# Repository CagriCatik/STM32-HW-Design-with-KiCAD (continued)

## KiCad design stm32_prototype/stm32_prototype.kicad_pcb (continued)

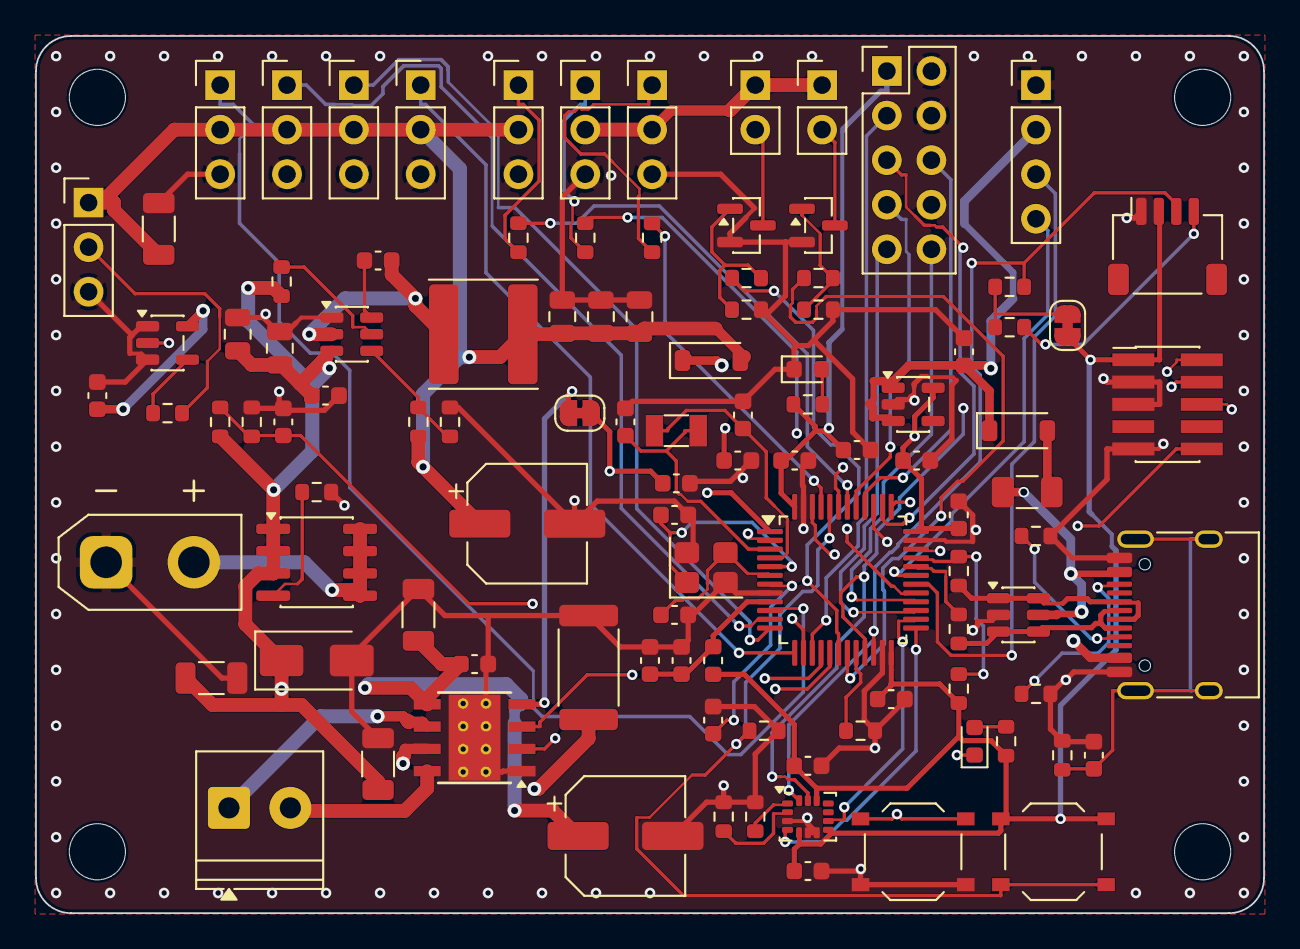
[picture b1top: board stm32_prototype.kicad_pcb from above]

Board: 4 copper layers, 70.0 x 50.0 mm, 108 parts (0 on the bottom side), 76 nets.

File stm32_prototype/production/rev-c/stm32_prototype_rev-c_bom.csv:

"Comment","Designator","Footprint","LCSC Part #"
"100n","C1,C2,C3,C5,C12,C15,C18,C19,C29,C31,C32,C33","Capacitor_SMD:C_0603_1608Metric","C14663"
"4.7u","C4","Capacitor_SMD:C_0603_1608Metric","C19666"
"10n","C6","Capacitor_SMD:C_0603_1608Metric","C57112"
"1u","C7,C24,C25","Capacitor_SMD:C_0603_1608Metric","C15849"
"15p","C8,C9","Capacitor_SMD:C_0603_1608Metric","C1644"
"22u 25V","C13,C14,C28,C34","Capacitor_SMD:C_1206_3216Metric","C12891"
"10u 25V","C16,C17","Capacitor_SMD:C_0805_2012Metric","C15850"
"22u 25V","C20,C21,C22","Capacitor_SMD:C_0805_2012Metric","C45783"
"4.7n","C23","Capacitor_SMD:C_0603_1608Metric","C53987"
"10u","C26","Capacitor_SMD:C_0603_1608Metric","C19702"
"100u 25V","C27,C30","Capacitor_SMD:CP_Elec_6.3x7.7","C72477"
"red","D1,D5","LED_SMD:LED_0603_1608Metric","C2286"
"SMAJ15A","D2","Diode_SMD:D_SMA","C353478"
"B5819W","D3,D4","Diode_SMD:D_SOD-123","C8598"
"500mA","F1","Fuse:Fuse_1206_3216Metric","C70077"
"600R@100MHz","FB1","Inductor_SMD:L_0603_1608Metric","C1002"
"XT30 battery 2S-3S","J1","Connector_AMASS:AMASS_XT30UPB-M_1x02_P5.0mm_Vertical","C428721"
"USB-C","J2","Connector_USB:USB_C_Receptacle_HRO_TYPE-C-31-M-12","C165948"
"MOTOR","J3","TerminalBlock_Phoenix:TerminalBlock_Phoenix_PT-1,5-2-3.5-H_1x02_P3.50mm_Horizontal","C474892"
"SERVO1","J4","Connector_PinHeader_2.54mm:PinHeader_1x03_P2.54mm_Vertical","C49257"
"SERVO2","J5","Connector_PinHeader_2.54mm:PinHeader_1x03_P2.54mm_Vertical","C49257"
"SERVO3","J6","Connector_PinHeader_2.54mm:PinHeader_1x03_P2.54mm_Vertical","C49257"
"SERVO4","J7","Connector_PinHeader_2.54mm:PinHeader_1x03_P2.54mm_Vertical","C49257"
"RC1","J8","Connector_PinHeader_2.54mm:PinHeader_1x03_P2.54mm_Vertical","C49257"
"RC2","J9","Connector_PinHeader_2.54mm:PinHeader_1x03_P2.54mm_Vertical","C49257"
"RC3","J10","Connector_PinHeader_2.54mm:PinHeader_1x03_P2.54mm_Vertical","C49257"
"LIGHT1","J11","Connector_PinHeader_2.54mm:PinHeader_1x02_P2.54mm_Vertical","C492401"
"LIGHT2","J12","Connector_PinHeader_2.54mm:PinHeader_1x02_P2.54mm_Vertical","C492401"
"Cortex-Debug","J13","Connector_PinHeader_1.27mm:PinHeader_2x05_P1.27mm_Vertical_SMD","C2935458"
"Qwiic","J14","Connector_JST:JST_SH_SM04B-SRSS-TB_1x04-1MP_P1.00mm_Horizontal","C160404"
"UART","J15","Connector_PinHeader_2.54mm:PinHeader_1x04_P2.54mm_Vertical","C2691448"
"WS2812","J17","Connector_PinHeader_2.54mm:PinHeader_1x03_P2.54mm_Vertical","C49257"
"3.3u","L1","Inductor_SMD:L_Sunlord_SWPA6045S","C83456"
"AO4407A","Q1","Package_SO:SOIC-8_3.9x4.9mm_P1.27mm","C16072"
"AO3400A","Q2,Q3","Package_TO_SOT_SMD:SOT-23","C20917"
"10k","R1,R2,R7,R9,R12,R25,R26","Resistor_SMD:R_0603_1608Metric","C25804"
"1k","R3,R16,R18,R19,R20","Resistor_SMD:R_0603_1608Metric","C21190"
"0R","R4,R5","Resistor_SMD:R_0603_1608Metric","C21189"
"1.5k","R6","Resistor_SMD:R_0603_1608Metric","C22843"
"33k","R8","Resistor_SMD:R_0603_1608Metric","C4216"
"100k","R10,R22,R24","Resistor_SMD:R_0603_1608Metric","C25803"
"56k","R11","Resistor_SMD:R_0603_1608Metric","C23206"
"5.1k","R13,R14","Resistor_SMD:R_0603_1608Metric","C23186"
"1M","R15","Resistor_SMD:R_0603_1608Metric","C22935"
"0.1R 2W","R17","Resistor_SMD:R_2512_6332Metric","C160587"
"100R","R21,R23","Resistor_SMD:R_0603_1608Metric","C22775"
"4.7k","R27,R28","Resistor_SMD:R_0603_1608Metric","C23162"
"330R","R29","Resistor_SMD:R_0603_1608Metric","C23138"
"BOOT0","SW1","Button_Switch_SMD:SW_Push_1P1T_XKB_TS-1187A","C318884"
"RESET","SW2","Button_Switch_SMD:SW_Push_1P1T_XKB_TS-1187A","C318884"
"STM32F103C8T6","U1","Package_QFP:LQFP-48_7x7mm_P0.5mm","C8734"
"TPS563201","U2","Package_TO_SOT_SMD:TSOT-23-6","C116592"
"USBLC6-2SC6","U3","Package_TO_SOT_SMD:SOT-23-6","C7519"
"AP2112K-3.3","U4","Package_TO_SOT_SMD:SOT-23-5","C51118"
"DRV8870","U5","Package_SO:Texas_HSOP-8-1EP_3.9x4.9mm_P1.27mm_ThermalVias","C86590"
"LSM6DS3TR-C","U6","Package_LGA:LGA-14_3x2.5mm_P0.5mm_LayoutBorder3x4y","C967633"
"SN74AHCT1G125","U7","Package_TO_SOT_SMD:SOT-23-5","C7484"
"8MHz","Y1","Crystal:Crystal_SMD_3225-4Pin_3.2x2.5mm","C2682775"

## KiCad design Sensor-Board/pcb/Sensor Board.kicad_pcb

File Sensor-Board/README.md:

# KiCAD_Sensor_Board
Gyroscope, accelerometer, magnetometer and imu sensor expansion board PCB design by usig KiCAD tool.

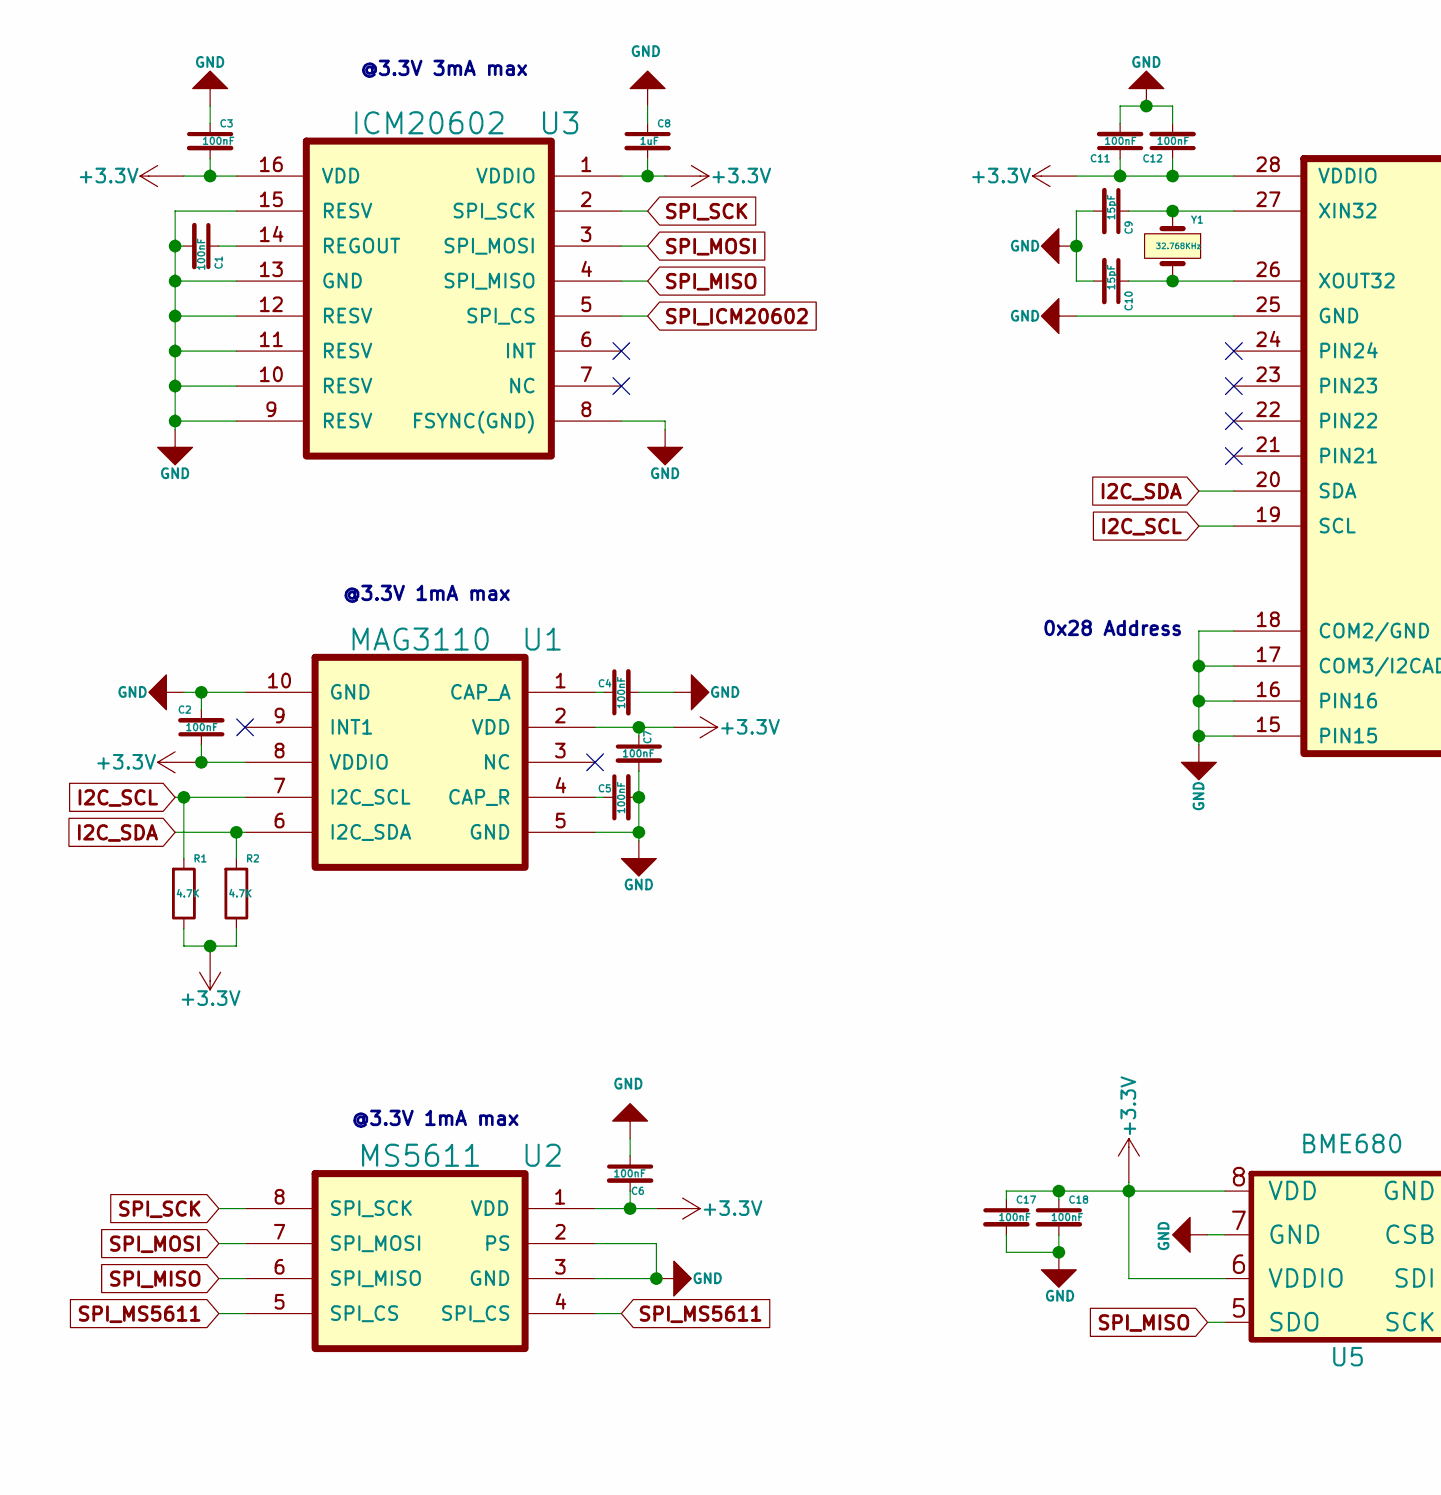
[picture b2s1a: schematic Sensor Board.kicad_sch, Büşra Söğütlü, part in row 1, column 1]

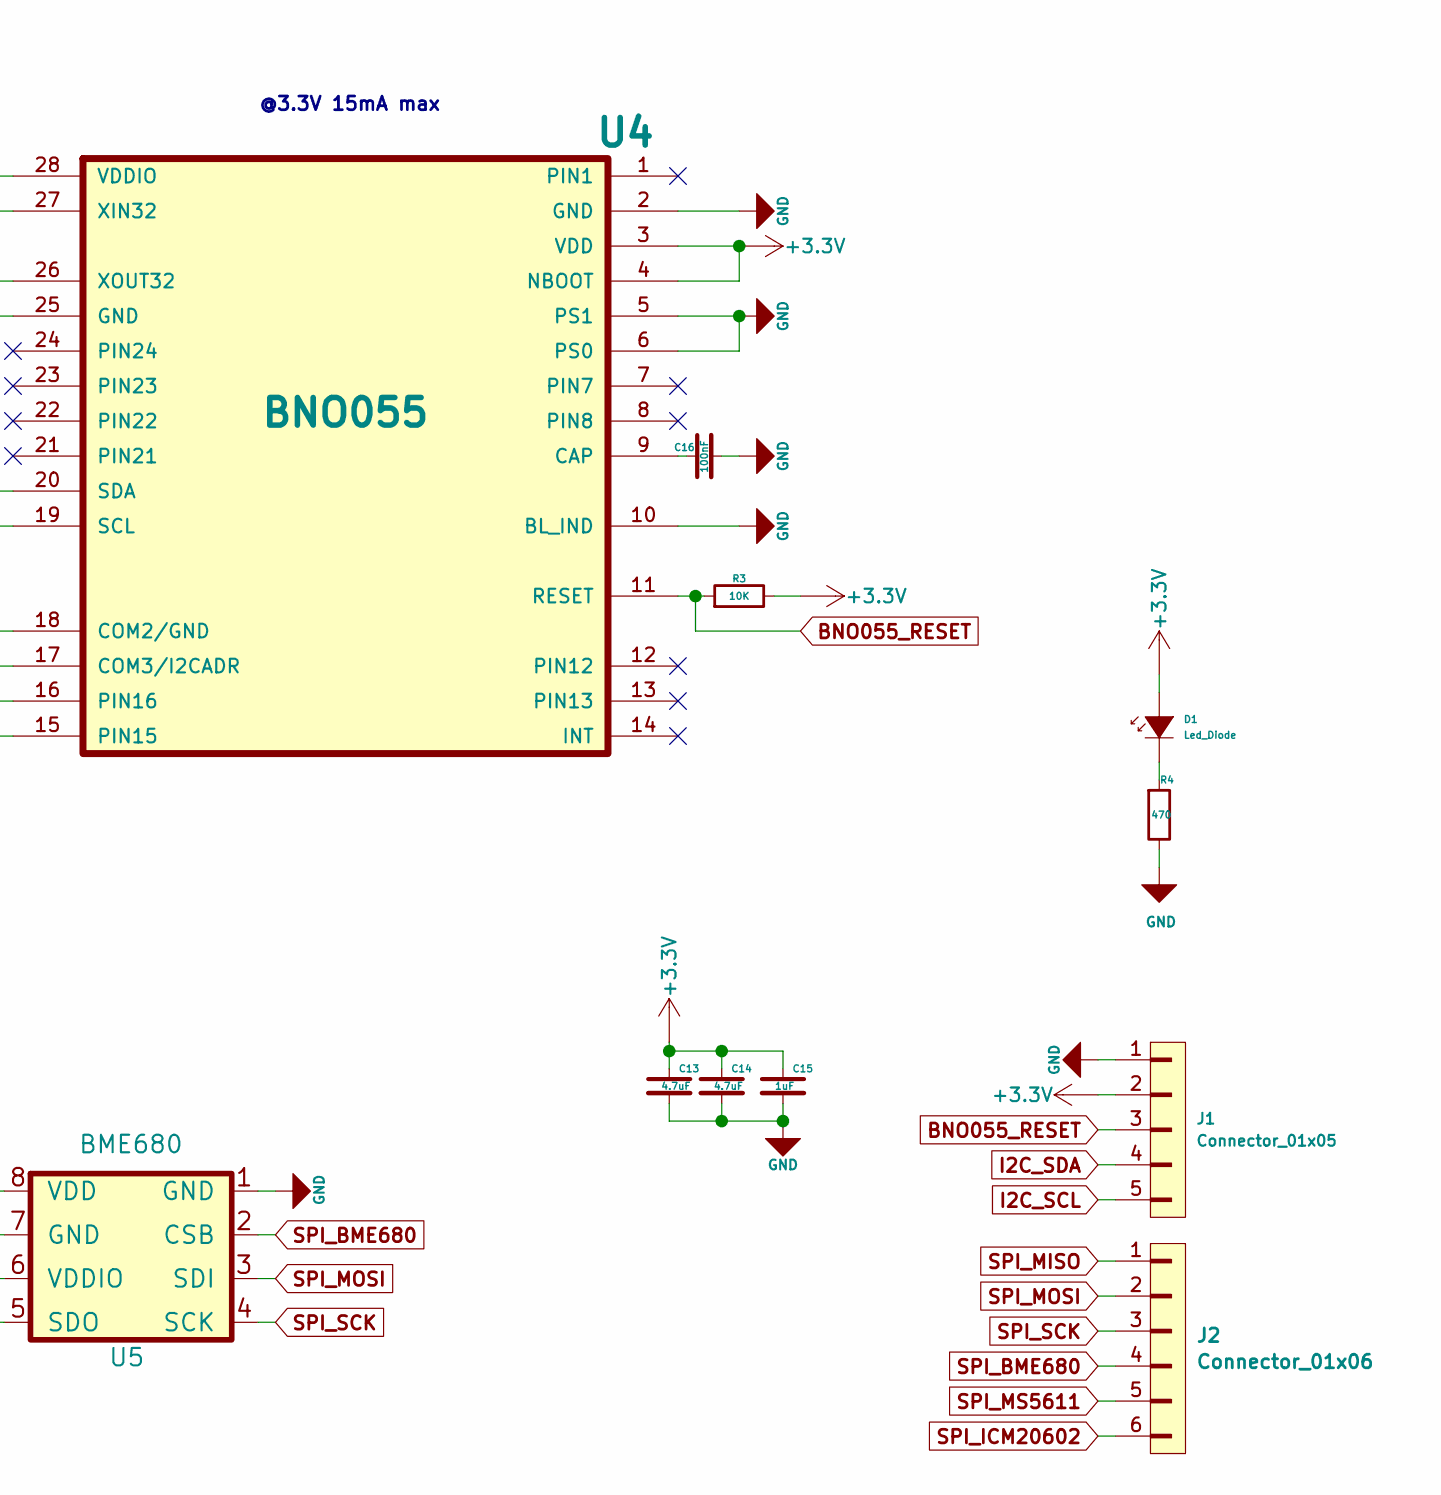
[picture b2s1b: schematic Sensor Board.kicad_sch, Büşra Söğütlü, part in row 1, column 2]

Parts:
C1, C2, C3, C4, C5, C6, C7, C11, C12, C16, C17, C18: 100nF; SMD_0402
C8, C15: 1uF; SMD_0603
C9, C10: 15pF; SMD_0402
C13, C14: 4.7uF; SMD_0603
D1: Led_Diode; Diode_0603
J1: Connector_01x05; PinHeader_1x5_P2.5mm
J2: Connector_01x06; PinHeader_1x6_P2.5mm
R1, R2: 4.7K; SMD_0402
R3: 10K; SMD_0402
R4: 470; SMD_0402
U1: MAG3110
U2: MS5611; MS56xx
U3: ICM20602; LGA16_3x3mm_P0.5mm
U4: BNO055; LGA28_3.8x5.2mm_P0.5mm
U5: BME680
Y1: 32.768KHz; ABS05_32.768KHz

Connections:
+3V3: C2.1, C3.2, C6.2, C7.1, C8.2, C11.1, C12.1, C13.1, C14.1, C15.1, C17.1, C18.1, D1.2 (A), J1.2, R1.2, R2.2, R3.2, U1.2 (VDD), U1.8 (VDDIO), U2.1 (VDD), U3.1 (VDDIO), U3.16 (VDD), U4.3 (VDD), U4.4 (NBOOT), U4.28 (VDDIO), U5.6 (VDDIO), U5.8 (VDD)
BNO055_RESET: J1.3, R3.1, U4.11 (RESET)
GND: C1.2, C2.2, C3.1, C4.2, C5.2, C6.1, C7.2, C8.1, C9.2, C10.2, C11.2, C12.2, C13.2, C14.2, C15.2, C16.2, C17.2, C18.2, J1.1, R4.2, U1.5 (GND), U1.10 (GND), U2.2 (PS), U2.3 (GND), U3.8 (FSYNC(GND)), U3.9 (RESV), U3.10 (RESV), U3.11 (RESV), U3.12 (RESV), U3.13 (GND), U3.15 (RESV), U4.2 (GND), U4.5 (PS1), U4.6 (PS0), U4.10 (BL_IND), U4.15 (PIN15), U4.16 (PIN16), U4.17 (COM3/I2CADR), U4.18 (COM2/GND), U4.25 (GND), U5.1 (GND), U5.7 (GND)
I2C_SCL: J1.5, R1.1, U1.7 (I2C_SCL), U4.19 (SCL)
I2C_SDA: J1.4, R2.1, U1.6 (I2C_SDA), U4.20 (SDA)
unnamed: C1.1, U3.14 (REGOUT)
unnamed: C4.1, U1.1 (CAP_A)
unnamed: C5.1, U1.4 (CAP_R)
unnamed: C9.1, U4.27 (XIN32), Y1.1
unnamed: C10.1, U4.26 (XOUT32), Y1.2
unnamed: C16.1, U4.9 (CAP)
unnamed: D1.1 (K), R4.1
SPI_BME680: J2.4, U5.2 (CSB)
SPI_ICM20602: J2.6, U3.5 (SPI_CS)
SPI_MISO: J2.1, U2.6 (SPI_MISO), U3.4 (SPI_MISO), U5.5 (SDO)
SPI_MOSI: J2.2, U2.7 (SPI_MOSI), U3.3 (SPI_MOSI), U5.3 (SDI)
SPI_MS5611: J2.5, U2.4 (SPI_CS), U2.5 (SPI_CS)
SPI_SCK: J2.3, U2.8 (SPI_SCK), U3.2 (SPI_SCK), U5.4 (SCK)

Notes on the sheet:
@3.3V 15mA max
@3.3V 3mA max
0x28 Address
@3.3V 1mA max

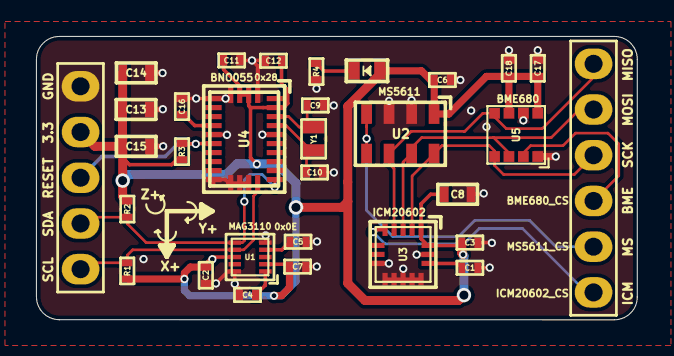
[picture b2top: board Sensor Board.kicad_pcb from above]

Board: 2 copper layers, 33.4 x 15.7 mm, 31 parts (0 on the bottom side), 18 nets.

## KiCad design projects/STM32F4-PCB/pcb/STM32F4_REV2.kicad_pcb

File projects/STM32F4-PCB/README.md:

# STM32F4-Reference-PCB

KiCad + STM32F4 + USB + Buck converter

- [Learn how to design your own STM32-based PCB](https://youtu.be/x_5rYfAyqq0)
  
- [Learn how to write firmware for the STM32 microcontroller](https://youtu.be/C7-8nUU6e3E)

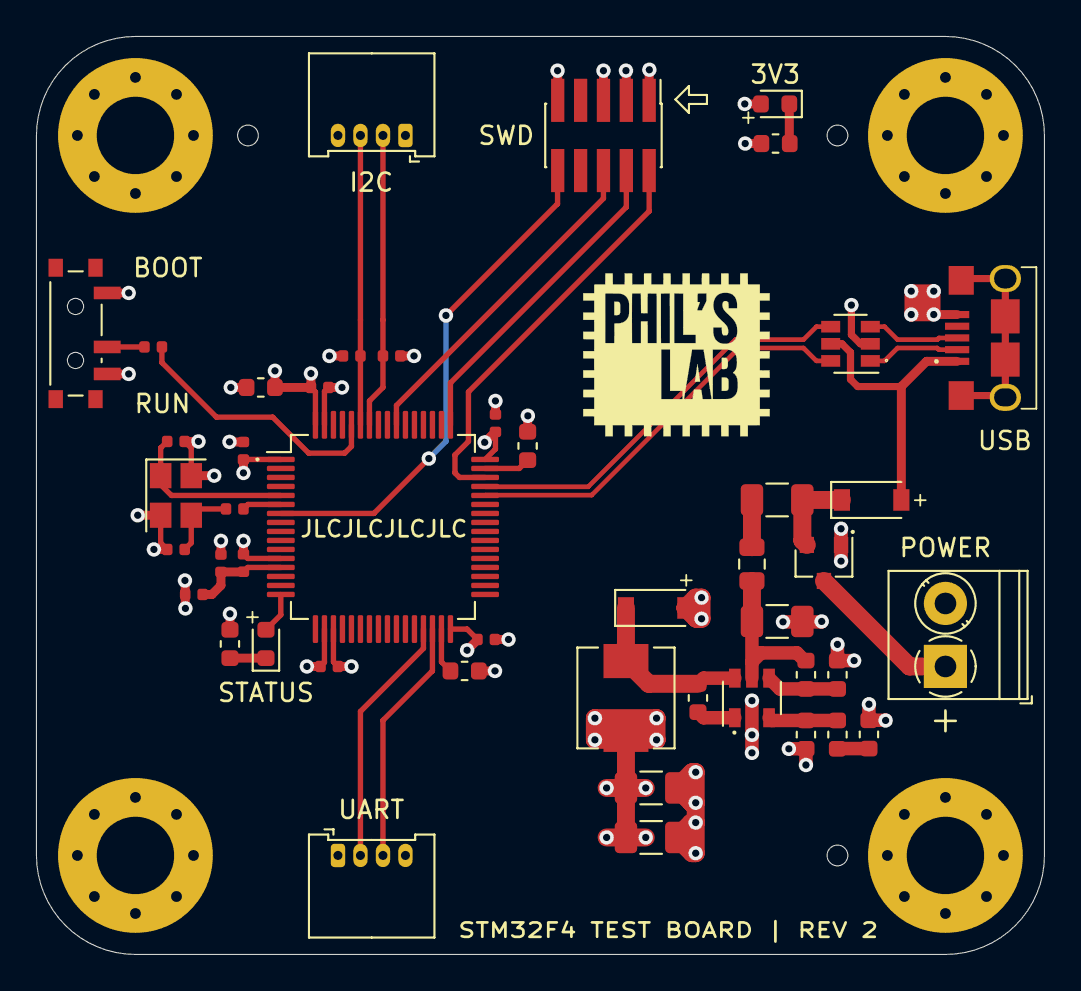
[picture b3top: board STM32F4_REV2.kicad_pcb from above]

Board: 4 copper layers, 56.0 x 51.0 mm, 50 parts (0 on the bottom side), 35 nets.

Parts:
C1, C2, C3: 10u; C_1206_3216Metric
C4: 10n; C_0603_1608Metric
C5: 4u7; C_0603_1608Metric
C6, C7, C8, C9, C10: 100n; C_0402_1005Metric
C11: 1u; C_0402_1005Metric
C12: 10n; C_0402_1005Metric
C13, C14: 2u2; C_0603_1608Metric
C15, C16: 12p; C_0402_1005Metric
D1, D2: B5819W; D_SOD-123
D3: RED; LED_0603_1608Metric
D4: BLUE; LED_0603_1608Metric
F1: 250mA; Fuse_1206_3216Metric
FB1: 600 @ 600MHz; L_0805_2012Metric
H1, H2, H3, H4: MountingHole_Pad; MountingHole_4.3mm_M4_Pad_Via
J1: Screw_Terminal_01x02; TerminalBlock_Phoenix_PT-1,5-2-3.5-H_1x02_P3.50mm_Horizontal
J2: SWD; PinHeader_2x05_P1.27mm_Vertical_SMD
J3, J4: Conn_01x04; Molex_PicoBlade_53048-0410_1x04_P1.25mm_Horizontal
J5: USB_B_Micro; USB_MICRO_B_101181930001LF
L1: 10u; L_Sunlord_MWSA0518_5.4x5.2mm
L2: 39n; L_0402_1005Metric
Q1: AO3401A; SOT-23
R1: 100k; R_0603_1608Metric
R2: 68k; R_0603_1608Metric
R3: 47k; R_0603_1608Metric
R4: 15k; R_0603_1608Metric
R5: 270; R_0603_1608Metric
R6: 1k; R_0603_1608Metric
R7: 10k; R_0402_1005Metric
R8: 47; R_0402_1005Metric
R9: 1k5; R_0603_1608Metric
R10, R11: 2k2; R_0402_1005Metric
SW1: SW_SPDT; SW_SPDT_PCM12
U1: MP2359DJ-LF-Z; SOT-23-6
U2: STM32F405RGT6; LQFP-64_10x10mm_P0.5mm
U3: USBLC6-2SC6; SOT-23-6
Y1: 16MHz; Crystal_SMD_3225-4Pin_3.2x2.5mm

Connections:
+3.3VA: C11.1, C12.1, L2.2, U2.13
+3V3: C2.1, C3.1, C5.1, C6.1, C7.1, C8.1, C9.1, C10.1, D3.2, J2.1, J3.1, J4.1, L1.2, L2.1, R3.1, R10.1, R11.1, SW1.1, U2.1, U2.19, U2.32, U2.48, U2.64
+5V: D1.2, J5.1, U3.5
+12V: J1.1, Q1.3
BOOT0: R7.2, U2.60
BUCK_BST: C4.2, U1.1
BUCK_EN: R1.2, R2.1, U1.4
BUCK_FB: R3.2, R4.1, U1.3
BUCK_IN: C1.1, FB1.1, R1.1, U1.5
BUCK_SW: C4.1, D2.1, L1.1, U1.6
GND: C1.2, C2.2, C3.2, C5.2, C6.2, C7.2, C8.2, C9.2, C10.2, C11.2, C12.2, C13.2, C14.2, C15.2, C16.2, D2.2, H1.1, H2.1, H3.1, H4.1, J1.2, J2.3, J2.5, J2.9, J3.4, J4.4, J5.5, Q1.1, R2.2, R5.2, R6.1, R9.1, SW1.3, U1.2, U2.12, U2.18, U2.63, U3.2, Y1.2, Y1.4
HSE_IN: C15.1, U2.5, Y1.1
HSE_OUT: R8.1, U2.6
I2C1_SCL: J3.2, R10.2, U2.58
I2C1_SDA: J3.3, R11.2, U2.59
LED_STATUS: D4.2, U2.16
NRST: J2.10, U2.7
unnamed: C13.1, U2.31
unnamed: C14.1, U2.47
unnamed: C16.1, R8.2, Y1.3
unnamed: D1.1, F1.2, Q1.2
unnamed: D3.1, R6.2
unnamed: D4.1, R9.2
unnamed: F1.1, FB1.2
unnamed: R4.2, R5.1
unnamed: R7.1, SW1.2
SWCLK: J2.4, U2.49
SWDIO: J2.2, U2.46
SWO: J2.6, U2.55
USART3_RX: J4.3, U2.30
USART3_TX: J4.2, U2.29
USB_CONN_D+: J5.3, U3.3
USB_CONN_D-: J5.2, U3.1
USB_D+: U2.45, U3.4
USB_D-: U2.44, U3.6

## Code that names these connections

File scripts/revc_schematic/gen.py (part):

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for n in libsym.pins(libsym.flat('MCU_ST_STM32F1', 'STM32F103C8Tx')):
    mcu_pins.setdefault(n['name'], []).append(n['num'])
special = {'VDD': '+3V3', 'VSS': 'GND', 'VSSA': 'GND', 'VDDA': 'VDDA', 'VBAT': 'VBAT_RTC', 'NRST': 'NRST',
           'BOOT0': 'BOOT0', 'PB2': 'BOOT1', 'PD0': 'HSE_IN', 'PD1': 'HSE_OUT', 'PA13': 'SWDIO', 'PA14': 'SWCLK',
           'PB3': 'SWO',
           # RC car functions
           'PA0': 'SERVO1', 'PA1': 'SERVO2', 'PA2': 'SERVO3', 'PA3': 'SERVO4',      # TIM2 CH1-4
           'PA4': 'VBAT_SENSE',                                                         # ADC12_IN4
           'PA6': 'MOTOR_IN1', 'PA7': 'MOTOR_IN2',                                      # TIM3 CH1/CH2
           'PB0': 'LIGHT1', 'PB1': 'LIGHT2',                                            # TIM3 CH3/CH4
           'PB6': 'RC_IN1', 'PB7': 'RC_IN2', 'PB8': 'RC_IN3',                           # TIM4 CH1-3, 5 V tolerant
           'PA9': 'UART_TX', 'PA10': 'UART_RX',                                         # USART1
           'PB10': 'I2C_SCL', 'PB11': 'I2C_SDA',                                        # I2C2
           'PB12': 'IMU_INT1', 'PB13': 'IMU_INT2',
           'PA8': 'LED_DATA'}                                                           # TIM1 CH1 + DMA, WS2812
u1 = {num: special.get(name, name) for name, nums in mcu_pins.items() for num in nums}
P(S, 'U', 'MCU_ST_STM32F1', 'STM32F103C8Tx', 'STM32F103C8T6', 'Package_QFP:LQFP-48_7x7mm_P0.5mm',
  'C8734', 'STM32F103C8T6', (80, 58), 0, u1)
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C(S, *C15P, (19, 30), 'HSE_IN')
C(S, *C15P, (31, 30), 'HSE_OUT')
P(S, 'Y', 'Device', 'Crystal', '32.768kHz', 'Crystal:Crystal_SMD_3215-2Pin_3.2x1.5mm', 'C95361', 'Q13FC13500049',
  (25, 45), 0, {'1': 'PC14', '2': 'PC15'}, dnp=True)
C(S, *C4P7, (19, 53), 'PC14', dnp=True)
C(S, *C4P7, (31, 53), 'PC15', dnp=True)
R(S, *R10K, (125, 25), 'BOOT0', 'GND')
P(S, 'SW', 'Switch', 'SW_Push', 'BOOT0', 'Button_Switch_SMD:SW_Push_1P1T_XKB_TS-1187A', 'C318884', 'TS-1187A-B-A-B',
  (135, 18), 0, {'1': '+3V3', '2': 'BOOT0'})
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  (135, 40), 0, {'1': 'NRST', '2': 'GND'})
R(S, *R1K, (125, 65), '+3V3', 'LED_USER_A', rot=90)
P(S, 'D', 'Device', 'LED', 'red', 'LED_SMD:LED_0603_1608Metric', 'C2286', 'KT-0603R',
  (135, 65), 180, {'2': 'LED_USER_A', '1': 'PC13'})
R(S, *R0, (125, 82), 'USB_D+', 'PA12', rot=90)
R(S, *R0, (125, 90), 'USB_D-', 'PA11', rot=90)
R(S, *R1K5, (140, 88), '+3V3', 'PA12')

# ================================================================ Power sheet (A3)
S = 'power'
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HDR(S, 4, 'UART', (20, 60), ['GND', '+5V', 'UART_TX', 'UART_RX'], 'C2691448', 'PZ254V-11-04P')
P(S, 'J', 'Connector_Generic', 'Conn_02x05_Odd_Even', 'EXPANSION', 'Connector_PinHeader_2.54mm:PinHeader_2x05_P2.54mm_Vertical',
  'C492422', 'PZ254V-12-10P', (60, 62), 0,
  {'1': '+3V3', '2': 'GND', '3': 'PA5', '4': 'GND', '5': 'PA15', '6': 'PB4', '7': 'PB5', '8': 'PB9', '9': 'PB14',
   '10': 'PB15'}, dnp=True)
# WS2812 / SK6812 chain (6 LEDs: front, sills, rear): 3.3 V data -> 74AHCT1G125 at 5 V -> 330R -> connector
P(S, 'U', '74xGxx', '74AHCT1G125', 'SN74AHCT1G125', 'Package_TO_SOT_SMD:SOT-23-5', 'C7484', 'SN74AHCT1G125DBVR',
  (130, 30), 0, {'1': 'GND', '2': 'LED_DATA', '3': 'GND', '4': 'LED_BUF', '5': '+5V'})
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    P(S, 'H', 'Mechanical', 'MountingHole', 'M3', 'MountingHole:MountingHole_3.2mm_M3', '', '', (85 + 6 * i, 70), 0, {})

NOTES = {
 'mcu': [((10, 108), 'Pin map: PA0-PA3 SERVO1-4 (TIM2 CH1-4) | PA4 VBAT_SENSE (ADC) | PA6/PA7 MOTOR_IN1/2 (TIM3 CH1/2)\n'
                     'PB0/PB1 LIGHT1/2 (TIM3 CH3/4) | PB6-PB8 RC_IN1-3 (TIM4 CH1-3, 5 V tolerant) | PA9/PA10 USART1\n'
                     'PB10/PB11 I2C2 (IMU + Qwiic) | PB12/PB13 IMU INT1/INT2 | PC13 user LED (low-active)\n'
                     'HSE 8 MHz, C_L = 12 pF: C = 2*(12 pF - 4 pF) = 16 pF -> 15 pF C0G. LSE optional (DNP).')],
 'power': [((10, 112), 'Battery 2S-3S LiPo (6-12.6 V) on XT30. AO4407A: reverse polarity protection (gate to GND).\n'
                       'SMAJ15A clamps transients. VBAT_SENSE = VBAT * 10k/43k (12.6 V -> 2.93 V).\n'
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                       'IN1/IN2 PWM from TIM3: forward/reverse/brake. Below 6.5 V (empty 2S) the driver locks out.\n'
                       'SERVO1-4: S / 5V / GND (use SERVO2 for an ESC; cut the ESC BEC red wire).\n'
                       'RC1-3 inputs: receiver PWM/PPM, powered from the servo rail, 1k series protection.')],
 'io': [((10, 75), 'IMU LSM6DS3TR-C on I2C2 at 0x6A (SA0 = GND), INT1 -> PB12, INT2 -> PB13.\n'
                   'Qwiic shares I2C2; 4.7k pull-ups, cut JP to remove. UART: GND 5V TX RX (Bluetooth/telemetry).\n'
                   'Expansion 2x5 (loose header): 3V3 GND PA5 GND PA15 PB4 PB5 PB9 PB14 PB15.\n'
                   'WS2812 output: 5V, DIN, GND. PA8 (TIM1 CH1, DMA) -> 74AHCT1G125 (5 V levels) -> 330R. 6 LEDs ~0.36 A.')],
}
SHEETS = [('mcu', 'MCU', 'A3', 2), ('power', 'Power', 'A3', 3), ('drive', 'Drive', 'A3', 4), ('io', 'IO', 'A3', 5)]
SHEETS_TITLES = [('mcu', 'STM32F103C8T6 core'), ('power', 'Battery, 5 V buck, USB-C, 3.3 V'),
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
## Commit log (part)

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2024-12-04 repo updated
2025-01-20 test deployment
2025-01-20 deploy: 34227209a61fe82c07bb1eed98911633add36b4a
2025-01-20 deploy: 3366728c56dde7a0cdc36f1d83be36d2784e1ae8
2025-01-20 deploy: 2da6d26eb32eaad3fad8e58dea2cdedb52f310f6
2025-01-20 Ignore the projects folder
2025-11-15 deploy updated
2025-11-21 deploy: 43f88f41e830746a612b464393d9c32d9b9f278d
2025-11-26 deploy: b4a9f93869e6d897b034c68497b7139adae8ddc8
2025-12-28 mkdocs..
2025-12-28 Deployed 47f6f15 with MkDocs version: 1.6.1
